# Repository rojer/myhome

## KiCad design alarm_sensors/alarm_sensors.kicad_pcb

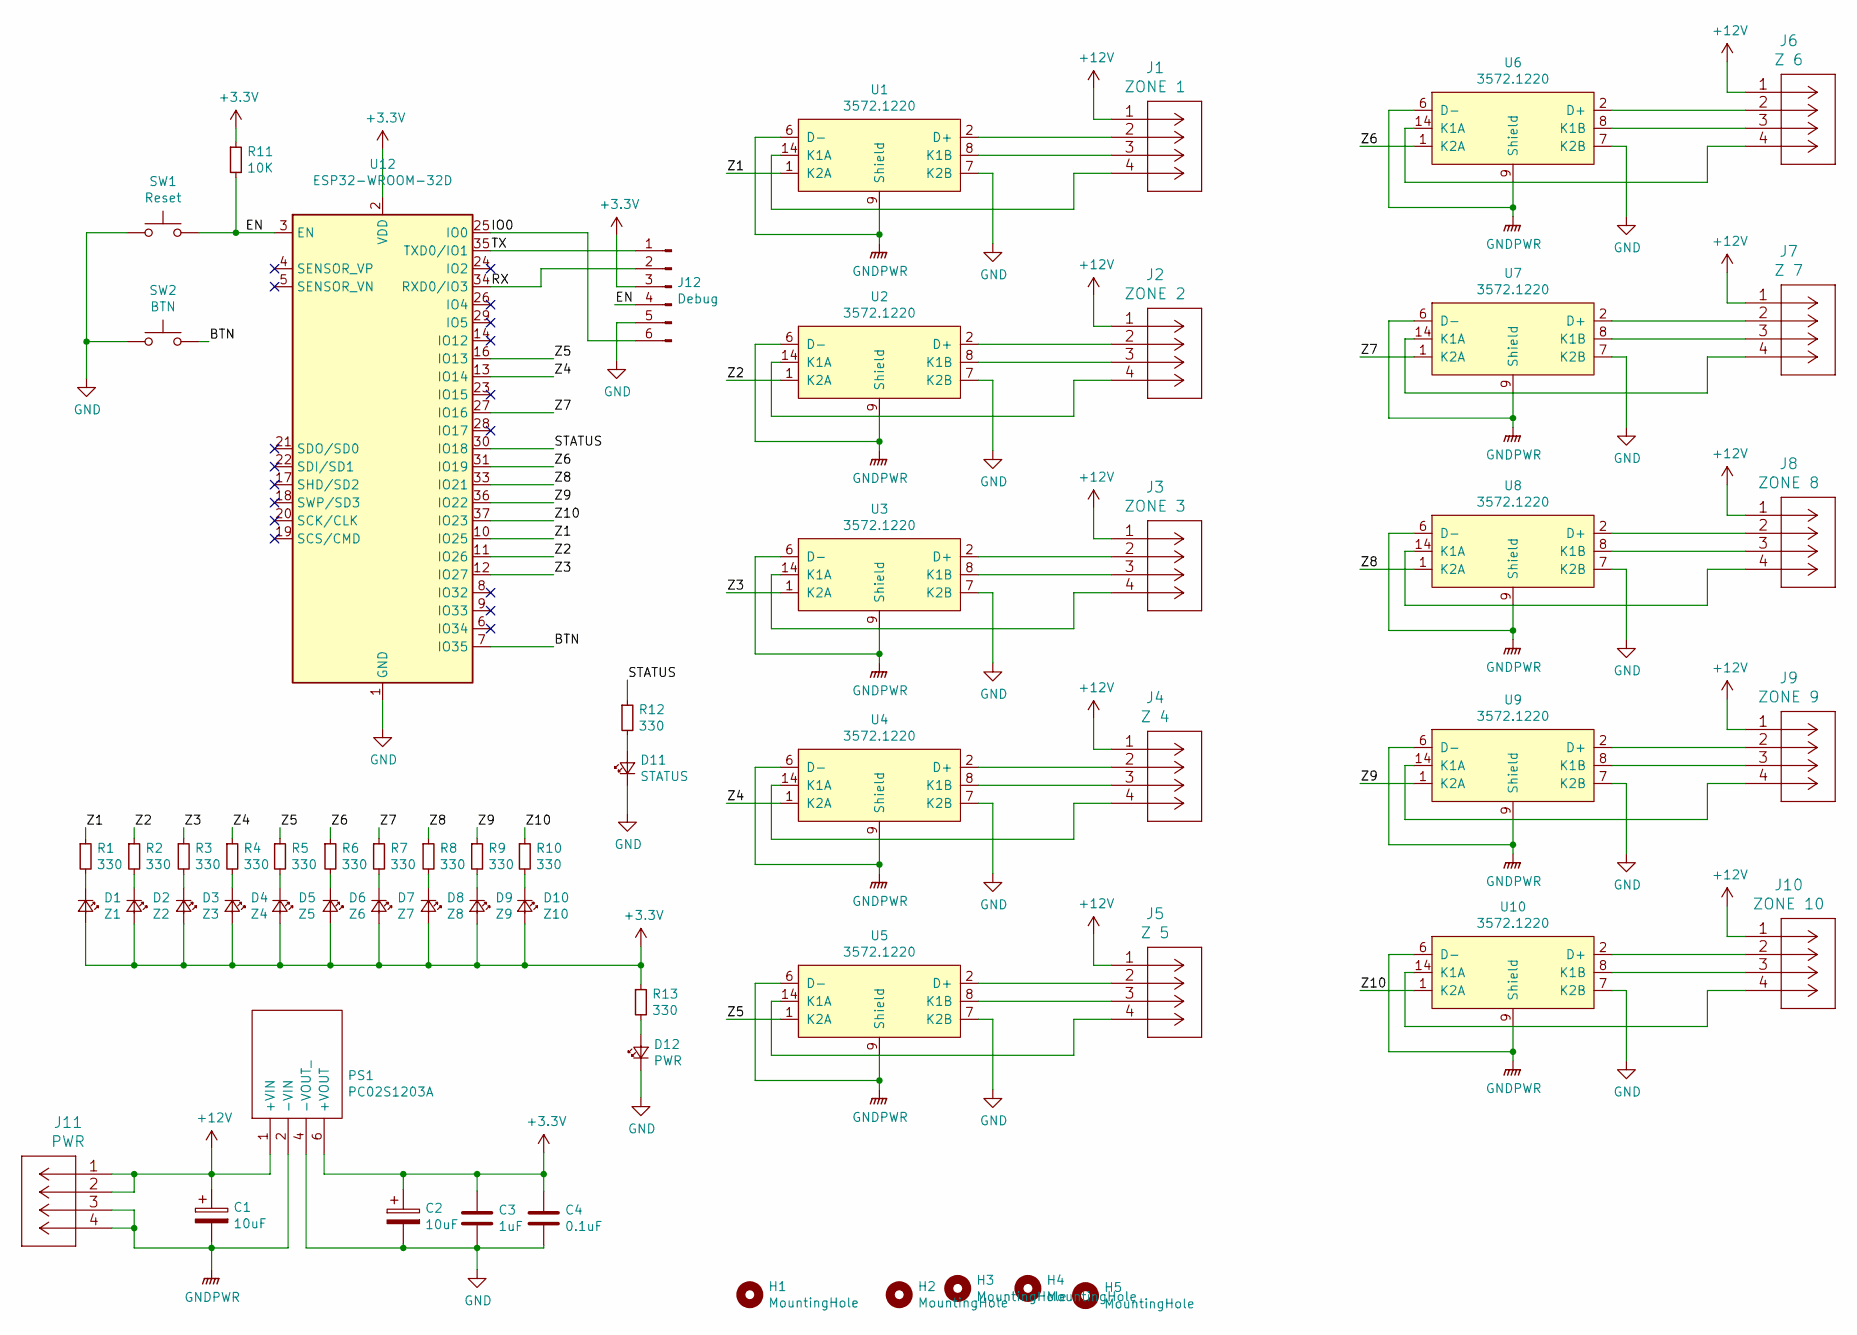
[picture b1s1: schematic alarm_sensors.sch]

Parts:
C1, C2: 10uF; CP_Radial_D5.0mm_P2.00mm
C3: 1uF; C_0603_1608Metric
C4: 0.1uF; C_0603_1608Metric
D1: Z1; LED_D3.0mm
D2: Z2; LED_D3.0mm
D3: Z3; LED_D3.0mm
D4: Z4; LED_D3.0mm
D5: Z5; LED_D3.0mm
D6: Z6; LED_D3.0mm
D7: Z7; LED_D3.0mm
D8: Z8; LED_D3.0mm
D9: Z9; LED_D3.0mm
D10: Z10; LED_D3.0mm
D11: STATUS; LED_D3.0mm
D12: PWR; LED_D3.0mm
H1: MountingHole; MountingHole_6mm
H2, H3, H4, H5: MountingHole; MountingHole_4mm
J1: ZONE 1; OSTVN04A150
J2: ZONE 2; OSTVN04A150
J3: ZONE 3; OSTVN04A150
J4: Z 4; OSTVN04A150
J5: Z 5; OSTVN04A150
J6: Z 6; OSTVN04A150
J7: Z 7; OSTVN04A150
J8: ZONE 8; OSTVN04A150
J9: ZONE 9; OSTVN04A150
J10: ZONE 10; OSTVN04A150
J11: PWR; OSTVN04A150
J12: Debug; PinHeader_1x06_P2.54mm_Vertical
PS1: PC02S1203A; Mouser Part Number 108-PC02S1203A
R1, R2, R3, R4, R5, R6, R7, R8, R9, R10, R12, R13: 330; R_0603_1608Metric
R11: 10K; R_0603_1608Metric
SW1: Reset; SW_PUSH_6mm
SW2: BTN; SW_PUSH_6mm
U1, U2, U3, U4, U5, U6, U7, U8, U9, U10: 3572.1220; DIP-14_W7.62mm_1267
U12: ESP32-WROOM-32D; ESP32-WROOM-32

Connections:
+3V3: C2.1, C3.1, C4.1, D1.2 (A), D2.2 (A), D3.2 (A), D4.2 (A), D5.2 (A), D6.2 (A), D7.2 (A), D8.2 (A), D9.2 (A), D10.2 (A), J12.3, PS1.6 (+VOUT), R11.1, R13.1, U12.2 (VDD)
+12V: C1.1, J1.1, J2.1, J3.1, J4.1, J5.1, J6.1, J7.1, J8.1, J9.1, J10.1, J11.1, J11.2, PS1.1 (+VIN)
/BTN: SW2.2, U12.7 (IO35)
/EN: J12.4, R11.2, SW1.2, U12.3 (EN)
/IO0: J12.6, U12.25 (IO0)
/RX: J12.2, U12.34 (RXD0/IO3)
/STATUS: R12.1, U12.30 (IO18)
/TX: J12.1, U12.35 (TXD0/IO1)
/Z1: R1.1, U1.1 (K2A), U12.10 (IO25)
/Z2: R2.1, U2.1 (K2A), U12.11 (IO26)
/Z3: R3.1, U3.1 (K2A), U12.12 (IO27)
/Z4: R4.1, U4.1 (K2A), U12.13 (IO14)
/Z5: R5.1, U5.1 (K2A), U12.16 (IO13)
/Z6: R6.1, U6.1 (K2A), U12.31 (IO19)
/Z7: R7.1, U7.1 (K2A), U12.27 (IO16)
/Z8: R8.1, U8.1 (K2A), U12.33 (IO21)
/Z9: R9.1, U9.1 (K2A), U12.36 (IO22)
/Z10: R10.1, U10.1 (K2A), U12.37 (IO23)
GND: C2.2, C3.2, C4.2, D11.1 (K), D12.1 (K), J12.5, PS1.4 (-VOUT_), SW1.1, SW2.1, U1.7 (K2B), U2.7 (K2B), U3.7 (K2B), U4.7 (K2B), U5.7 (K2B), U6.7 (K2B), U7.7 (K2B), U8.7 (K2B), U9.7 (K2B), U10.7 (K2B), U12.1 (GND), U12.15 (GND), U12.38 (GND), U12.39 (GND)
GNDPWR: C1.2, J11.3, J11.4, PS1.2 (-VIN), U1.6 (D-), U1.9 (Shield), U2.6 (D-), U2.9 (Shield), U3.6 (D-), U3.9 (Shield), U4.6 (D-), U4.9 (Shield), U5.6 (D-), U5.9 (Shield), U6.6 (D-), U6.9 (Shield), U7.6 (D-), U7.9 (Shield), U8.6 (D-), U8.9 (Shield), U9.6 (D-), U9.9 (Shield), U10.6 (D-), U10.9 (Shield)
unnamed: D1.1 (K), R1.2
unnamed: D2.1 (K), R2.2
unnamed: D3.1 (K), R3.2
unnamed: D4.1 (K), R4.2
unnamed: D5.1 (K), R5.2
unnamed: D6.1 (K), R6.2
unnamed: D7.1 (K), R7.2
unnamed: D8.1 (K), R8.2
unnamed: D9.1 (K), R9.2
unnamed: D10.1 (K), R10.2
unnamed: D11.2 (A), R12.2
unnamed: D12.2 (A), R13.2
unnamed: J1.2, U1.2 (D+)
unnamed: J1.3, U1.8 (K1B)
unnamed: J1.4, U1.14 (K1A)
unnamed: J2.2, U2.2 (D+)
unnamed: J2.3, U2.8 (K1B)
unnamed: J2.4, U2.14 (K1A)
unnamed: J3.2, U3.2 (D+)
unnamed: J3.3, U3.8 (K1B)
unnamed: J3.4, U3.14 (K1A)
unnamed: J4.2, U4.2 (D+)
unnamed: J4.3, U4.8 (K1B)
unnamed: J4.4, U4.14 (K1A)
unnamed: J5.2, U5.2 (D+)
unnamed: J5.3, U5.8 (K1B)
unnamed: J5.4, U5.14 (K1A)
unnamed: J6.2, U6.2 (D+)
unnamed: J6.3, U6.8 (K1B)
unnamed: J6.4, U6.14 (K1A)
unnamed: J7.2, U7.2 (D+)
unnamed: J7.3, U7.8 (K1B)
unnamed: J7.4, U7.14 (K1A)
unnamed: J8.2, U8.2 (D+)
unnamed: J8.3, U8.8 (K1B)
unnamed: J8.4, U8.14 (K1A)
unnamed: J9.2, U9.2 (D+)
unnamed: J9.3, U9.8 (K1B)
unnamed: J9.4, U9.14 (K1A)
unnamed: J10.2, U10.2 (D+)
unnamed: J10.3, U10.8 (K1B)
unnamed: J10.4, U10.14 (K1A)

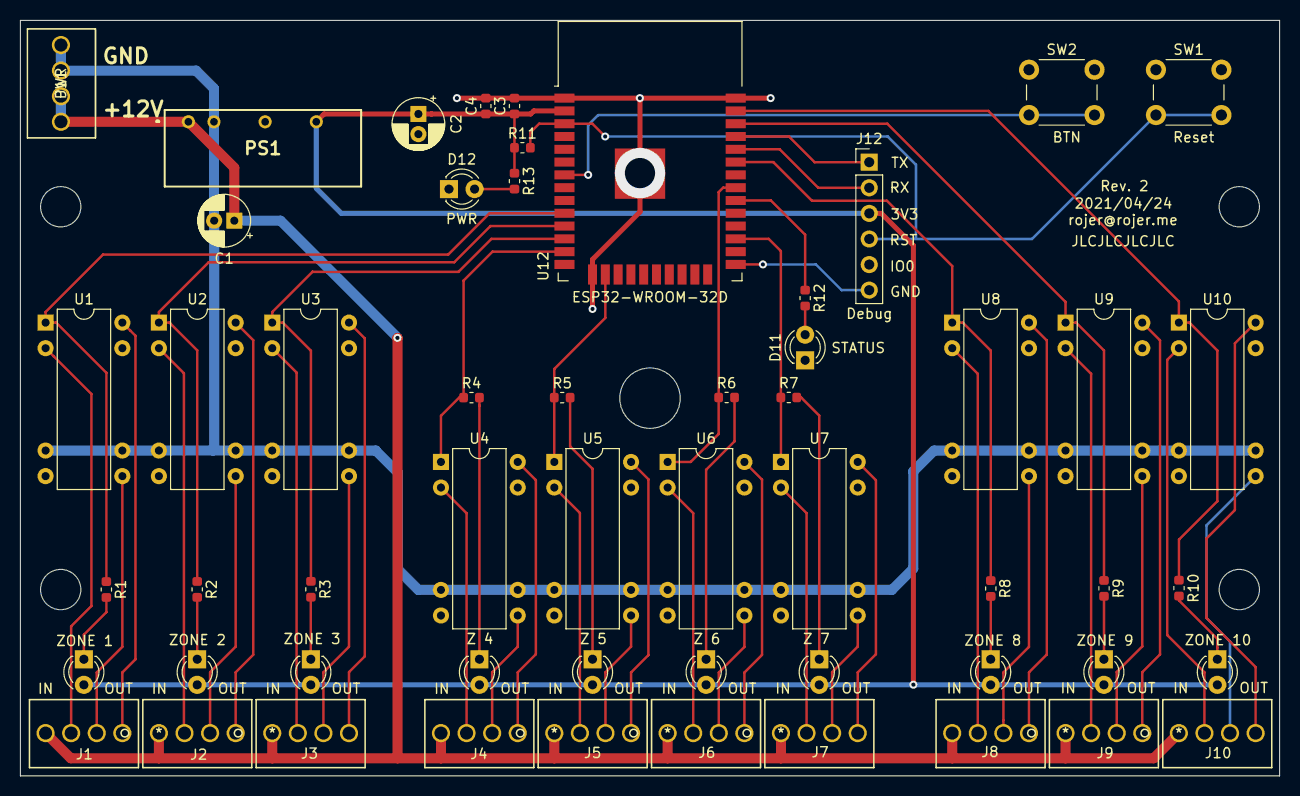
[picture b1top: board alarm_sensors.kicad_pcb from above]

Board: 2 copper layers, 125.0 x 75.0 mm, 60 parts (0 on the bottom side), 62 nets.

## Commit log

2015-03-17 hello world!
    scp sucks.
2015-03-17 Add nice to remote commands.
2015-05-28 Ignore everything, use git add -f to add stuff
2017-04-03 Add hub fw
2018-01-28 Rewrite in C, add heater control
2018-06-10 New stuff
2018-06-11 Heater control loop
2018-10-15 A bunch of changes
    * Rewrite HWS to use DS18B20 temp sensor
    * Update hub to check thresholds for S0 and S1
    Should really merge hws into temp, have it support both types of sensors
2019-01-26 Report to server
2019-01-27 Move things
2019-01-27 Remove unneeded var
2019-01-30 Add cron support, some other changes
2019-01-30 When leaving manual mode, turn heating off but not on
2019-02-01 Re-format with a proper config
2019-02-02 Downgrade message to debug
2019-04-02 GetTemp RPC
2019-04-02 Sensor data refactoring
2019-04-02 Sensor names
2019-04-04 GetLimits, SetLimits RPCs
2019-04-04 Implement graph UI
    * Press the temperature or humidity of a sensor to open a brand new fragment which displays the history of readings
    * NB: Currently the data is randomly and locally generated, however, this will soon fetch data from a web server
2019-04-04 Add target temperature control
    * Control the target temperature of a given sensor
2019-04-04 Fetch graph data from server
    * Retrieve historical data from an online server
    * Show accurate values when a point on the graph is selected
    * Show maximum and minimum values
2019-04-04 Move application into separate directory
2019-04-04 Move firmware to a subdir
2019-04-04 Remove conf1.json from temp sensor fw
2019-04-04 Make graph UI more reachable (#3)
    * This commit fixes #3
2019-04-04 Min and max values reflect data on the screen (#7)
    * This commit fixes #7
2019-04-04 Run on UI thread
2019-04-05 Replace hardcoded JSON strings with serializer
    * Use Gson to serialize a Java object instead of sending manually typed strings
2019-04-05 Tidy up
    * Use camel case method names
    * Remove unused code
    * Misc changes
2019-04-05 Check for WiFi before connecting to web socket
    * Remind the user if the device is not connected to WiFi that the websocket cannot connect
2019-04-05 Highlighted value persists after switching date (#6)
    * This commit fixes #6
2019-04-05 Display target temperature on graph (#8)
    * This commit fixes #8
2019-04-05 Update the UI automatically (#5)
    * As soon as new data is received on the web socket, update the UI to reflect changes
    * When the application is loaded automatically send a request to connect to the web socket and start loading data
2019-04-05 Extract hardcoded text to strings.xml
    * Move hardcoded String values into strings.xml
    * Remove unnecessary Log calls
2019-04-05 Request Hub URL on first app opening (#2)
    * When the app is first opened (or the URLs are not set) show a dialog to ask for user input
    * Installation note: when upgrading from previous builds of the app, I recommend clearing application data
    * This commit fixes #2
2019-04-05 Tidy up navigation drawer
    * Group the sensor elements together and add a group title
2019-04-05 Re-evaluate heater rules after setting limit
2019-04-05 Allow small duration values
2019-04-05 Re-eval on ReportTemp
2019-04-07 Check in the data server code
2019-04-07 Fix websocket origin check
2019-04-26 hub: Add heater control on/off setting, pin to 2.13.1
2019-04-29 Fix heater control status logic
2019-07-07 Port hub to ESP32
2019-07-17 Switch to UDP for sensor data reports
2019-08-10 Update to 2.15.0 + UDP reconnect
2019-08-28 Check in table schema
2019-08-28 Add a basic index page to the data server
2019-08-28 Fix handler order
2019-08-28 Add support for BME680 sensor
2019-09-02 hub: Add Sensor.Data handler, update to mos 2.15
2019-09-02 Report sensor names with BME680 data
2019-09-30 Initial Xavax support, reporting only for now
2019-10-02 bt-relay: Fix change detection logic
2019-10-19 Add bogus Xavax data detection logic
2019-10-19 Add dns-sd, advertise device ID as name
2019-10-19 clang-format code
2019-11-03 New method name for reporting data
2020-03-08 Xavax script changes
2020-03-13 temp: Support multiple sensor addresses
2020-04-23 Use manual mode again
2020-04-24 Hacky solution for valve control
2020-04-28 Add firmware for PIR sensor
2020-05-04 Save hub data every 60 seconds to speed up recovery
2020-06-29 Add sids to xavax_map
2020-06-29 Disable heating during the day when it's warm outside
2020-08-07 Make it possible to enable/disable limit entry without setting min/max
2020-08-21 Add 10 more limits
2020-08-22 Xavax sensors update
2020-08-22 C++ rewrite, mutliple outputs logic
2020-08-22 Add Sensor.DataMulti
2020-08-23 Use Sensor.Data and Sensor.DataMulti
2020-08-24 Fix memory leak in Sensor.Data
2020-08-24 Remove Sensor.ReportTemp, we don't need it anymore
2020-08-24 Enable control logic by default
2020-08-24 Add light sensor support to the sensor firmware
2020-08-28 Add output state to GetOutputs
2020-08-28 Add bh1750_mtime
2020-08-29 Force control reeval on limits change
2020-09-06 fix xavax map
2020-09-06 Change BH1750 to HIGH_RES_2 mode
2020-09-06 Add file logger library to hub
2020-10-26 Update map
2020-10-26 Remove hub_light module
    Lighting control is now handled by generic control mechanism
2020-10-26 Export limit evaluation status under SID 99
    Subid is the id of the limit
2020-10-26 Report no more than 3 sensors per pass
    To avoid RPC queue overflows
2020-10-27 Minor fix
2020-11-01 Update thresholds for xavax sensors from target temperature
2020-12-27 Add reboot after 5 minutes of disconnected wifi
2021-04-03 Add file-logger to the temp sensor
2021-04-03 Use mgos::Timer
2021-05-22 Add VEML7700 light sensor support
2021-07-01 SRF05 support
2021-09-06 Add firmware for the alarm_sensors board
2021-09-06 Add alarm_sensors board design
2021-09-06 Do not send a response if none is required
2021-09-06 Fix alam-sensor button input
    GPIO35 doesn't haave an internal pull-up, move to GPIO32.
2021-09-07 Rebuild hub to update deps
2021-09-09 Add HT100 support to xavax.py
2021-11-12 bt-relay: Fix leak when removing sensor entries
2021-12-06 Bump version of bt-relay for rebuild
2021-12-13 Rewrite in C++, add support for XiaoMi sensor w/ ATS fw
2021-12-26 bt-relay: Add rpc-service-gattc
2022-01-16 Improve bogus data fitering for Xavax sensors
2022-01-16 Tweakbogus value detections some more
2022-01-16 Spread reporting a bit
2022-01-18 Fix bogus readings detection for Xavax
2022-01-24 Fix uninitialized members
2022-02-08 Add support for Xiaomi PVVX advertising format
2022-05-15 bt-relay: Add scan_duration_ms
2022-05-15 Add another TRV
2022-05-16 hub: Rewrite hub data handling in C++
2022-05-17 Add limit dependencies
2022-06-04 SRF05 data reporting
2022-06-19 Add ethernet driver to ESP32 builds
2022-06-19 SRF05: Use last temp sensor reading if available
2022-07-14 SRF05: Report max distance, not avg
    Since we only expect it to increase
2022-07-28 SRF05: Increase count of samples to 60
2022-08-25 Use a different library for DS18B20 support
2022-08-28 Make number of SRF05 readings and interval configurable
2022-12-12 Also output unknown part of adv data
2022-12-13 bt-relay: Disable scan while OTA is in progress
2023-01-29 Add go mod
2023-01-29 Log invalid requests
2023-01-29 bt-relay: Better handling of scan start/stop during OTA and reboots
2023-01-29 bt-relay/BTSensorXavax: Better handling of bogus data
    If it looks like the data is bogus, wait for 2 mins before accepting it.
2023-05-05 Airlift as BT relay
2023-05-05 bt-relay: Reboot if haven't seen any scan results for 10 minutes
    Workaround for stuck BT stack
2023-11-28 Fix parsing of MiPVVX advertisements
    Newer fw versions include flags
2024-11-10 Update scan settings
2025-01-04 bt-relay: Add BTHome data parser
2025-01-04 Threshold updates for BluTRV
2025-05-25 bt-relay: mgos->shos
2025-06-24 Update for scan API change

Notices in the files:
parts and their libraries:
Copyright 2016 Accelerated Designs. All rights reserved.
